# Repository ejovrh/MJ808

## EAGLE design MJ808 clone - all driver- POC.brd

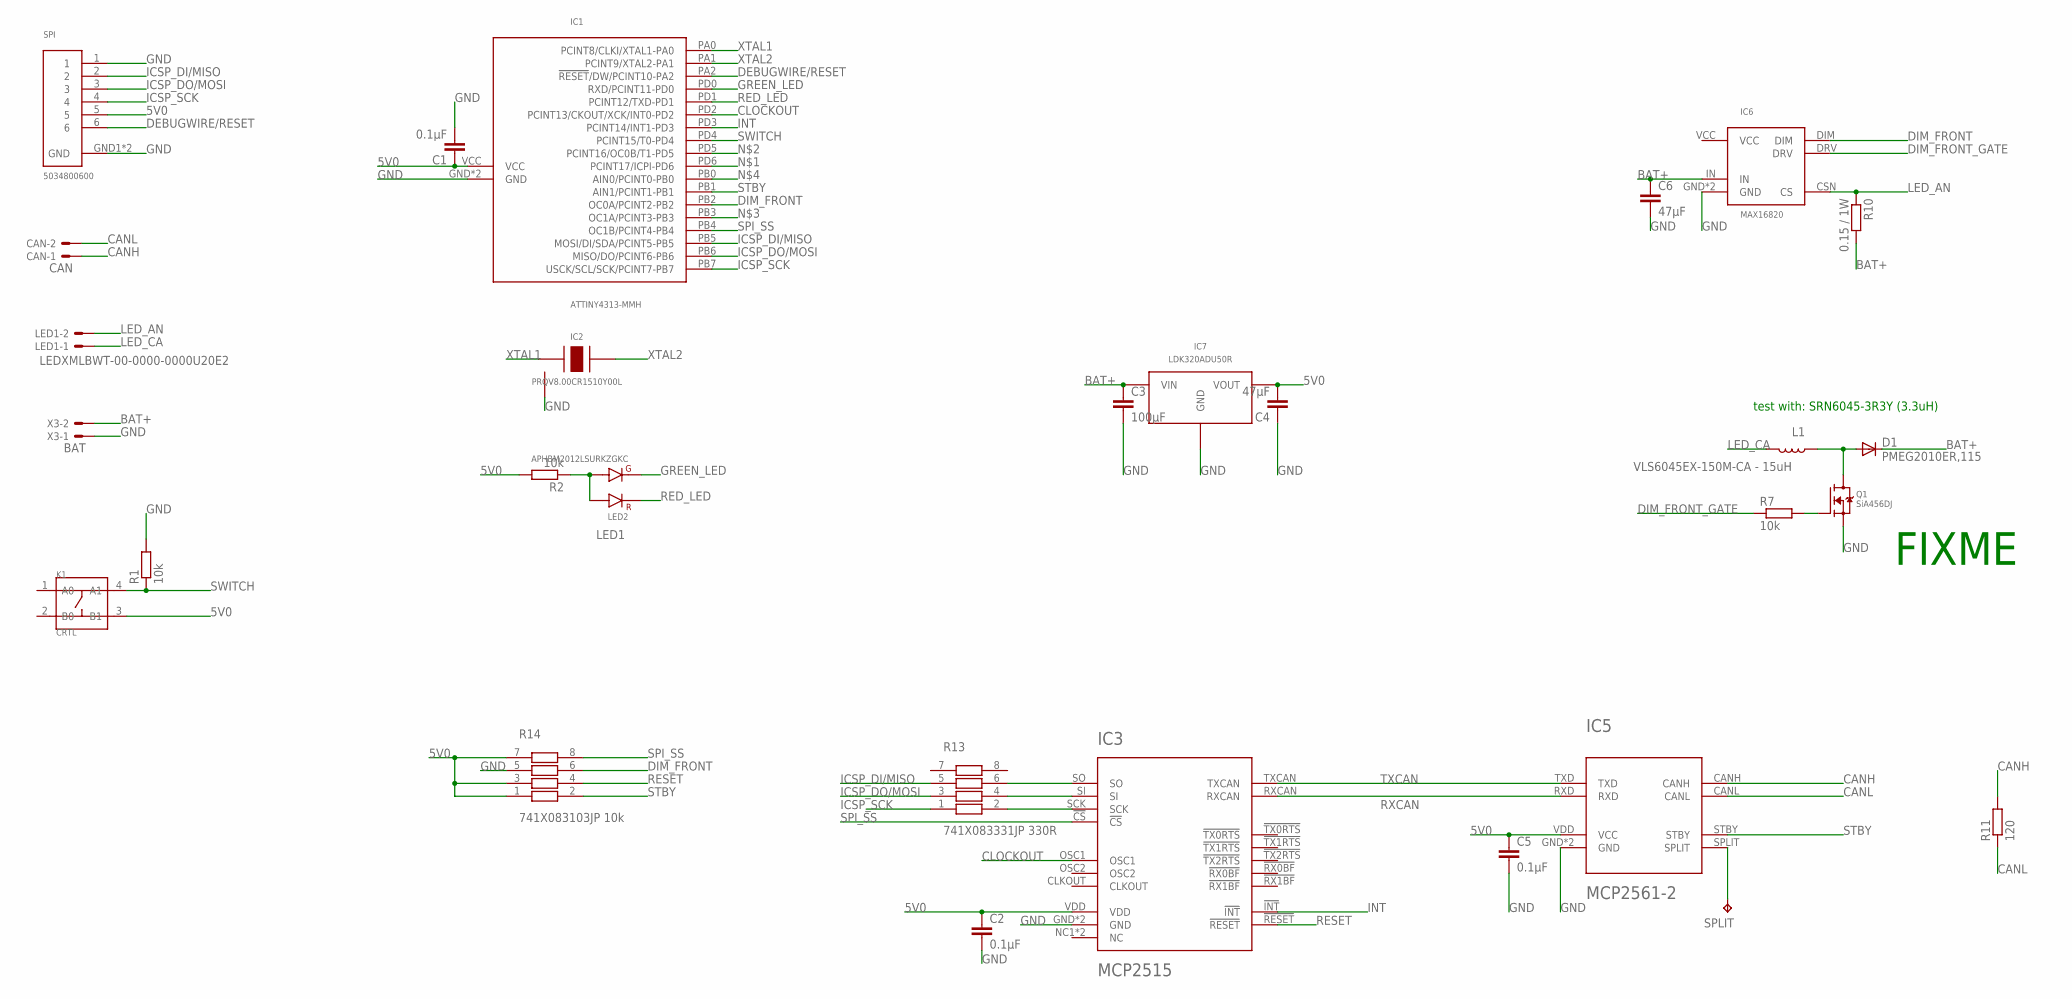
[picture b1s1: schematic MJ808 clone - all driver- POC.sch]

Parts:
C1, C2, C5: 0.1μF; C0402
C3: 100μF; C1206
C4, C6: 47μF; C0805
CAN: CAN; 22-23-2021
D1: PMEG2010ER,115; SOD123
IC1: ATTINY4313-MMH; VQFN-20
IC2: PRQV8.00CR1510Y00L; SMT
IC3: MCP2515; QFN20
IC5: MCP2561-2; DFN10
IC6: MAX16820; TDFN-6-EP
IC7: LDK320ADU50R; SOT-89
K1: CRTL; SW4-SMD-6.0X6.0X5.0MM
L1: VLS6045EX-150M-CA - 15uH; SRN6045
LED1: LEDXMLBWT-00-0000-0000U20E2; 22-23-2021
LED2: APHBM2012LSURKZGKC; SMD
Q1: SiA456DJ; SC-70-6
R1, R2, R7: 10k; R0402
R10: 0.15 / 1W; R1210
R11: 120; R0805
R13: 741X083331JP 330R; 0402
R14: 741X083103JP 10k; 0402
SPI: 5034800600; SMT
SPLIT: TPB2,54; B2,54
X3: BAT; 22-23-2021

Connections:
5V0: C1.1, C2.1, C4.2, C5.1, IC1.VCC, IC3.VDD, IC5.VDD (VCC), IC7.VOUT, K1.3 (B1), R2.2, R14.1, R14.3, R14.7, SPI.5
BAT+: C3.1, C6.1, D1.C, IC6.IN, IC7.VIN, R10.2, X3.2
CANH: CAN.1, IC5.CANH, R11.2
CANL: CAN.2, IC5.CANL, R11.1
CLOCKOUT: IC1.PD2 (PCINT13/CKOUT/XCK/INT0-PD2), IC3.OSC1
DEBUGWIRE/RESET: IC1.PA2 (!RESET!/DW/PCINT10-PA2), SPI.6
DIM_BRAKE_DRAIN: D1.A, L1.1, Q1.D
DIM_FRONT: IC1.PB2 (OC0A/PCINT2-PB2), IC6.DIM, R14.6
DIM_FRONT_GATE: IC6.DRV, R7.1
GATE: Q1.G, R7.2
GND: C1.2, C2.2, C3.2, C4.1, C5.2, C6.2, IC1.GND, IC1.GND1 (GND), IC2.GND, IC3.GND, IC3.GND6 (GND), IC5.GND, IC5.VSS (GND), IC6.GND, IC6.GND1 (GND), IC7.GND, Q1.S, R1.2, R14.5, SPI.1, SPI.GND1 (GND), SPI.GND2 (GND), X3.1
GREEN_LED: IC1.PD0 (RXD/PCINT11-PD0), LED2.3
ICSP_DI/MISO: IC1.PB5 (MOSI/DI/SDA/PCINT5-PB5), R13.5, SPI.2
ICSP_DO/MOSI: IC1.PB6 (MISO/DO/PCINT6-PB6), R13.3, SPI.3
ICSP_SCK: IC1.PB7 (USCK/SCL/SCK/PCINT7-PB7), R13.1, SPI.4
INT: IC1.PD3 (PCINT14/INT1-PD3), IC3.!INT!
LED1: LED2.1, LED2.4, R2.1
LED_AN: IC6.CSN (CS), LED1.2, R10.1
LED_CA: L1.2, LED1.1
RED_LED: IC1.PD1 (PCINT12/TXD-PD1), LED2.2
RESET: IC3.!RESET!, R14.4
RXCAN: IC3.RXCAN, IC5.RXD
SPI_MISO: IC3.SO, R13.6
SPI_MOSI: IC3.SI, R13.4
SPI_SCK: IC3.SCK, R13.2
SPI_SS: IC1.PB4 (OC1B/PCINT4-PB4), IC3.!CS!, R14.8
SPLIT: IC5.SPLIT, SPLIT.TP
STBY: IC1.PB1 (AIN1/PCINT1-PB1), IC5.STBY, R14.2
SWITCH: IC1.PD4 (PCINT15/T0-PD4), K1.4 (A1), R1.1
TXCAN: IC3.TXCAN, IC5.TXD
VCC: IC6.VCC
XTAL1: IC1.PA0 (PCINT8/CLKI/XTAL1-PA0), IC2.XTAL1
XTAL2: IC1.PA1 (PCINT9/XTAL2-PA1), IC2.XTAL2

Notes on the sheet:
FIXME
test with: SRN6045-3R3Y (3.3uH)

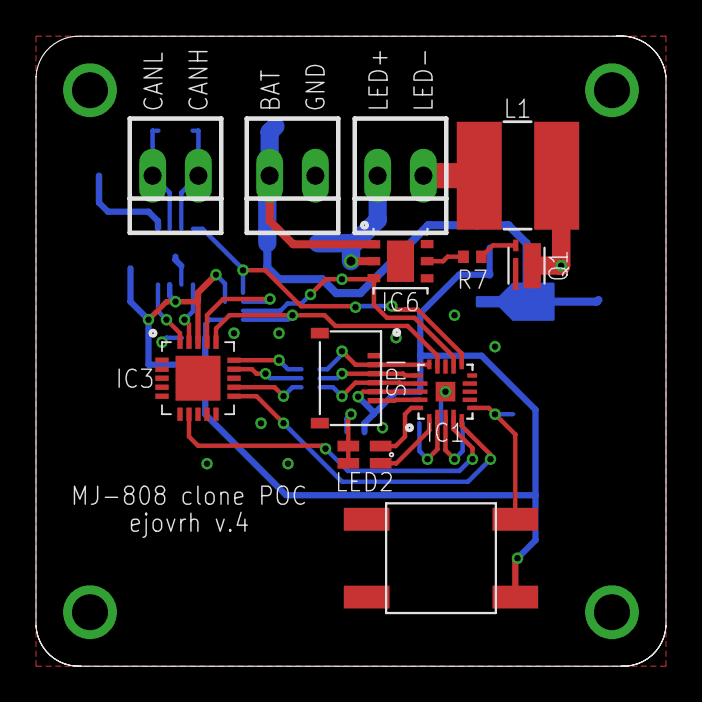
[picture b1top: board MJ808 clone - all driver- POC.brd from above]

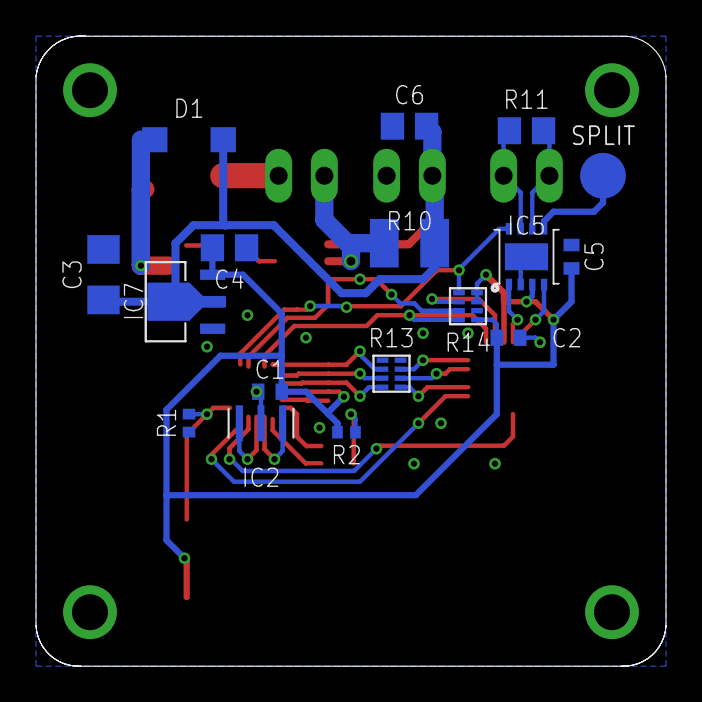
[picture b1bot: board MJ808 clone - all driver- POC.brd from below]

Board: 2 copper layers, 35.0 x 35.0 mm, 29 parts (17 on the bottom side), 32 nets.

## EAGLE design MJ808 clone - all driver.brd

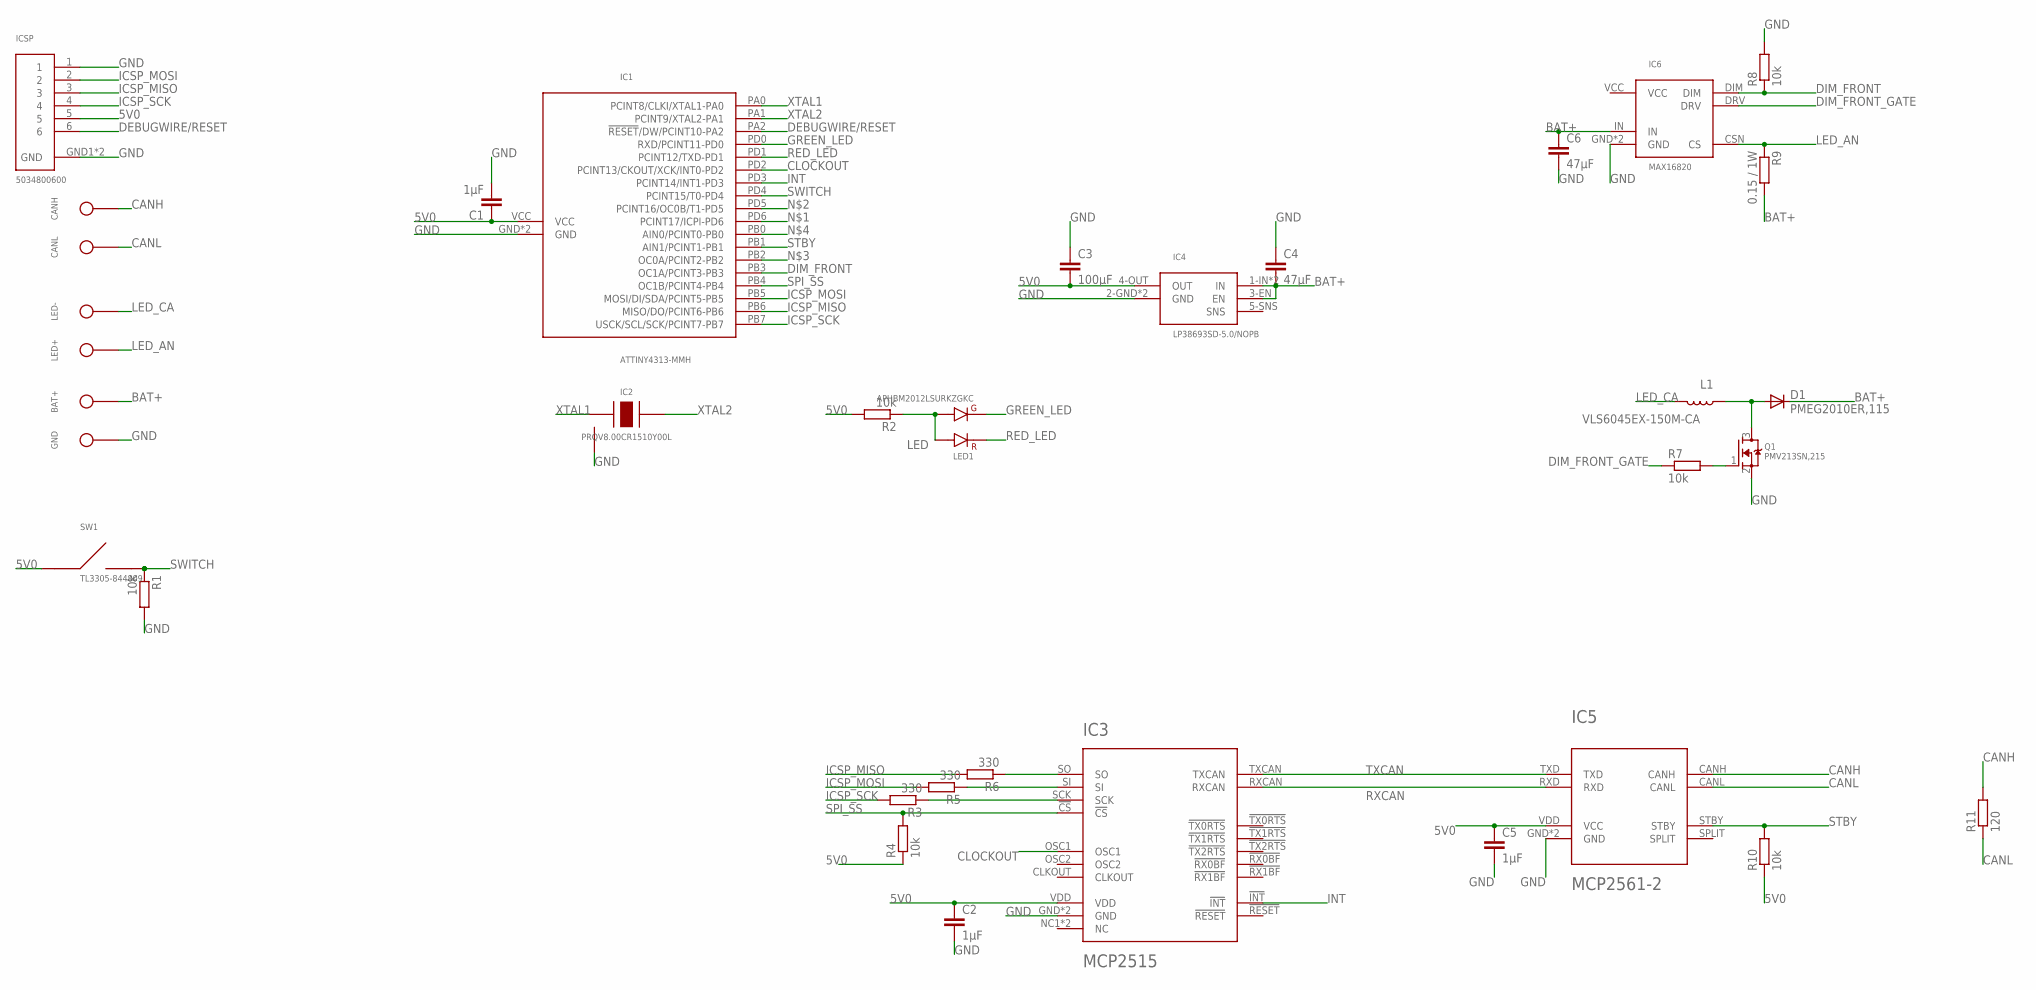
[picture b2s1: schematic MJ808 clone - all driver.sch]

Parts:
BAT+: LiIon + Terminal; TH
C1, C2, C5: 1μF; C0402
C3: 100μF; C1206
C4, C6: 47μF; C0805
CANH: CAN high; TH
CANL: CAN low; TH
D1: PMEG2010ER,115; SOD123
GND: LiIon - Terminal; TH
IC1: ATTINY4313-MMH; VQFN-20
IC2: PRQV8.00CR1510Y00L; SMT
IC3: MCP2515; QFN20
IC4: LP38693SD-5.0/NOPB; WSON6
IC5: MCP2561-2; DFN10
IC6: MAX16820; TDFN-6-EP
ICSP: 5034800600; SMT
L1: VLS6045EX-150M-CA; SRN6045
LED1: APHBM2012LSURKZGKC; SMD
LED+: LED anode; TH
LED-: LED cathode; TH
Q1: PMV213SN,215; SOT23
R1, R2, R4, R7, R8, R10: 10k; R0402
R3, R5, R6: 330; R0402
R9: 0.15 / 1W; R1210
R11: 120; R0805
SW1: TL3305-844809; SMD

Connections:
5V0: C1.1, C2.1, C3.2, C5.1, IC1.VCC, IC3.VDD, IC4.4-OUT (OUT), IC5.VDD (VCC), ICSP.5, R2.2, R4.1, R10.1, SW1.1, SW1.2
BAT+: BAT+.TP$1, C4.2, C6.1, D1.C, IC4.1-IN (IN), IC4.3-EN (EN), IC4.6-IN (IN), IC6.IN, R9.2
CANH: CANH.TP$1, IC5.CANH, R11.2
CANL: CANL.TP$1, IC5.CANL, R11.1
CLOCKOUT: IC1.PD2 (PCINT13/CKOUT/XCK/INT0-PD2), IC3.OSC1
DEBUGWIRE/RESET: IC1.PA2 (!RESET!/DW/PCINT10-PA2), ICSP.6
DIM_BRAKE_DRAIN: D1.A, L1.1, Q1.3 (D)
DIM_FRONT: IC1.PB3 (OC1A/PCINT3-PB3), IC6.DIM, R8.1
DIM_FRONT_GATE: IC6.DRV, R7.1
GATE: Q1.1 (G), R7.2
GND: C1.2, C2.2, C3.1, C4.1, C5.2, C6.2, GND.TP$1, IC1.GND, IC1.GND1 (GND), IC2.GND, IC3.GND, IC3.GND6 (GND), IC4.2-GND (GND), IC4.GND1 (GND), IC5.GND, IC5.VSS (GND), IC6.GND, IC6.GND1 (GND), ICSP.1, ICSP.GND1 (GND), ICSP.GND2 (GND), Q1.2 (S), R1.2, R8.2
GREEN_LED: IC1.PD0 (RXD/PCINT11-PD0), LED1.3
ICSP_MISO: IC1.PB6 (MISO/DO/PCINT6-PB6), ICSP.3, R6.2
ICSP_MOSI: IC1.PB5 (MOSI/DI/SDA/PCINT5-PB5), ICSP.2, R5.2
ICSP_SCK: IC1.PB7 (USCK/SCL/SCK/PCINT7-PB7), ICSP.4, R3.2
INT: IC1.PD3 (PCINT14/INT1-PD3), IC3.!INT!
LED: LED1.1, LED1.4, R2.1
LED_AN: IC6.CSN (CS), LED+.TP$1, R9.1
LED_CA: L1.2, LED-.TP$1
RED_LED: IC1.PD1 (PCINT12/TXD-PD1), LED1.2
RXCAN: IC3.RXCAN, IC5.RXD
SPI_MISO: IC3.SO, R6.1
SPI_MOSI: IC3.SI, R5.1
SPI_SCK: IC3.SCK, R3.1
SPI_SS: IC1.PB4 (OC1B/PCINT4-PB4), IC3.!CS!, R4.2
STBY: IC1.PB1 (AIN1/PCINT1-PB1), IC5.STBY, R10.2
SWITCH: IC1.PD4 (PCINT15/T0-PD4), R1.1, SW1.3, SW1.4
TXCAN: IC3.TXCAN, IC5.TXD
VCC: IC6.VCC
XTAL1: IC1.PA0 (PCINT8/CLKI/XTAL1-PA0), IC2.XTAL1
XTAL2: IC1.PA1 (PCINT9/XTAL2-PA1), IC2.XTAL2

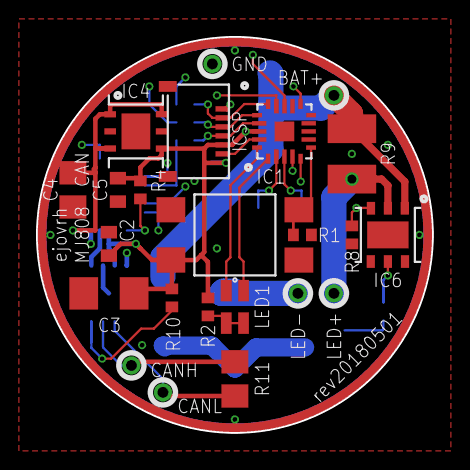
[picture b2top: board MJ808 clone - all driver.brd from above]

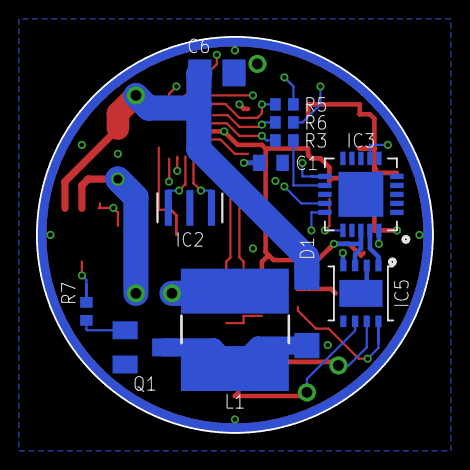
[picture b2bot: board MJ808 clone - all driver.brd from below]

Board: 4 copper layers, 22.0 x 22.0 mm, 35 parts (12 on the bottom side), 30 nets.

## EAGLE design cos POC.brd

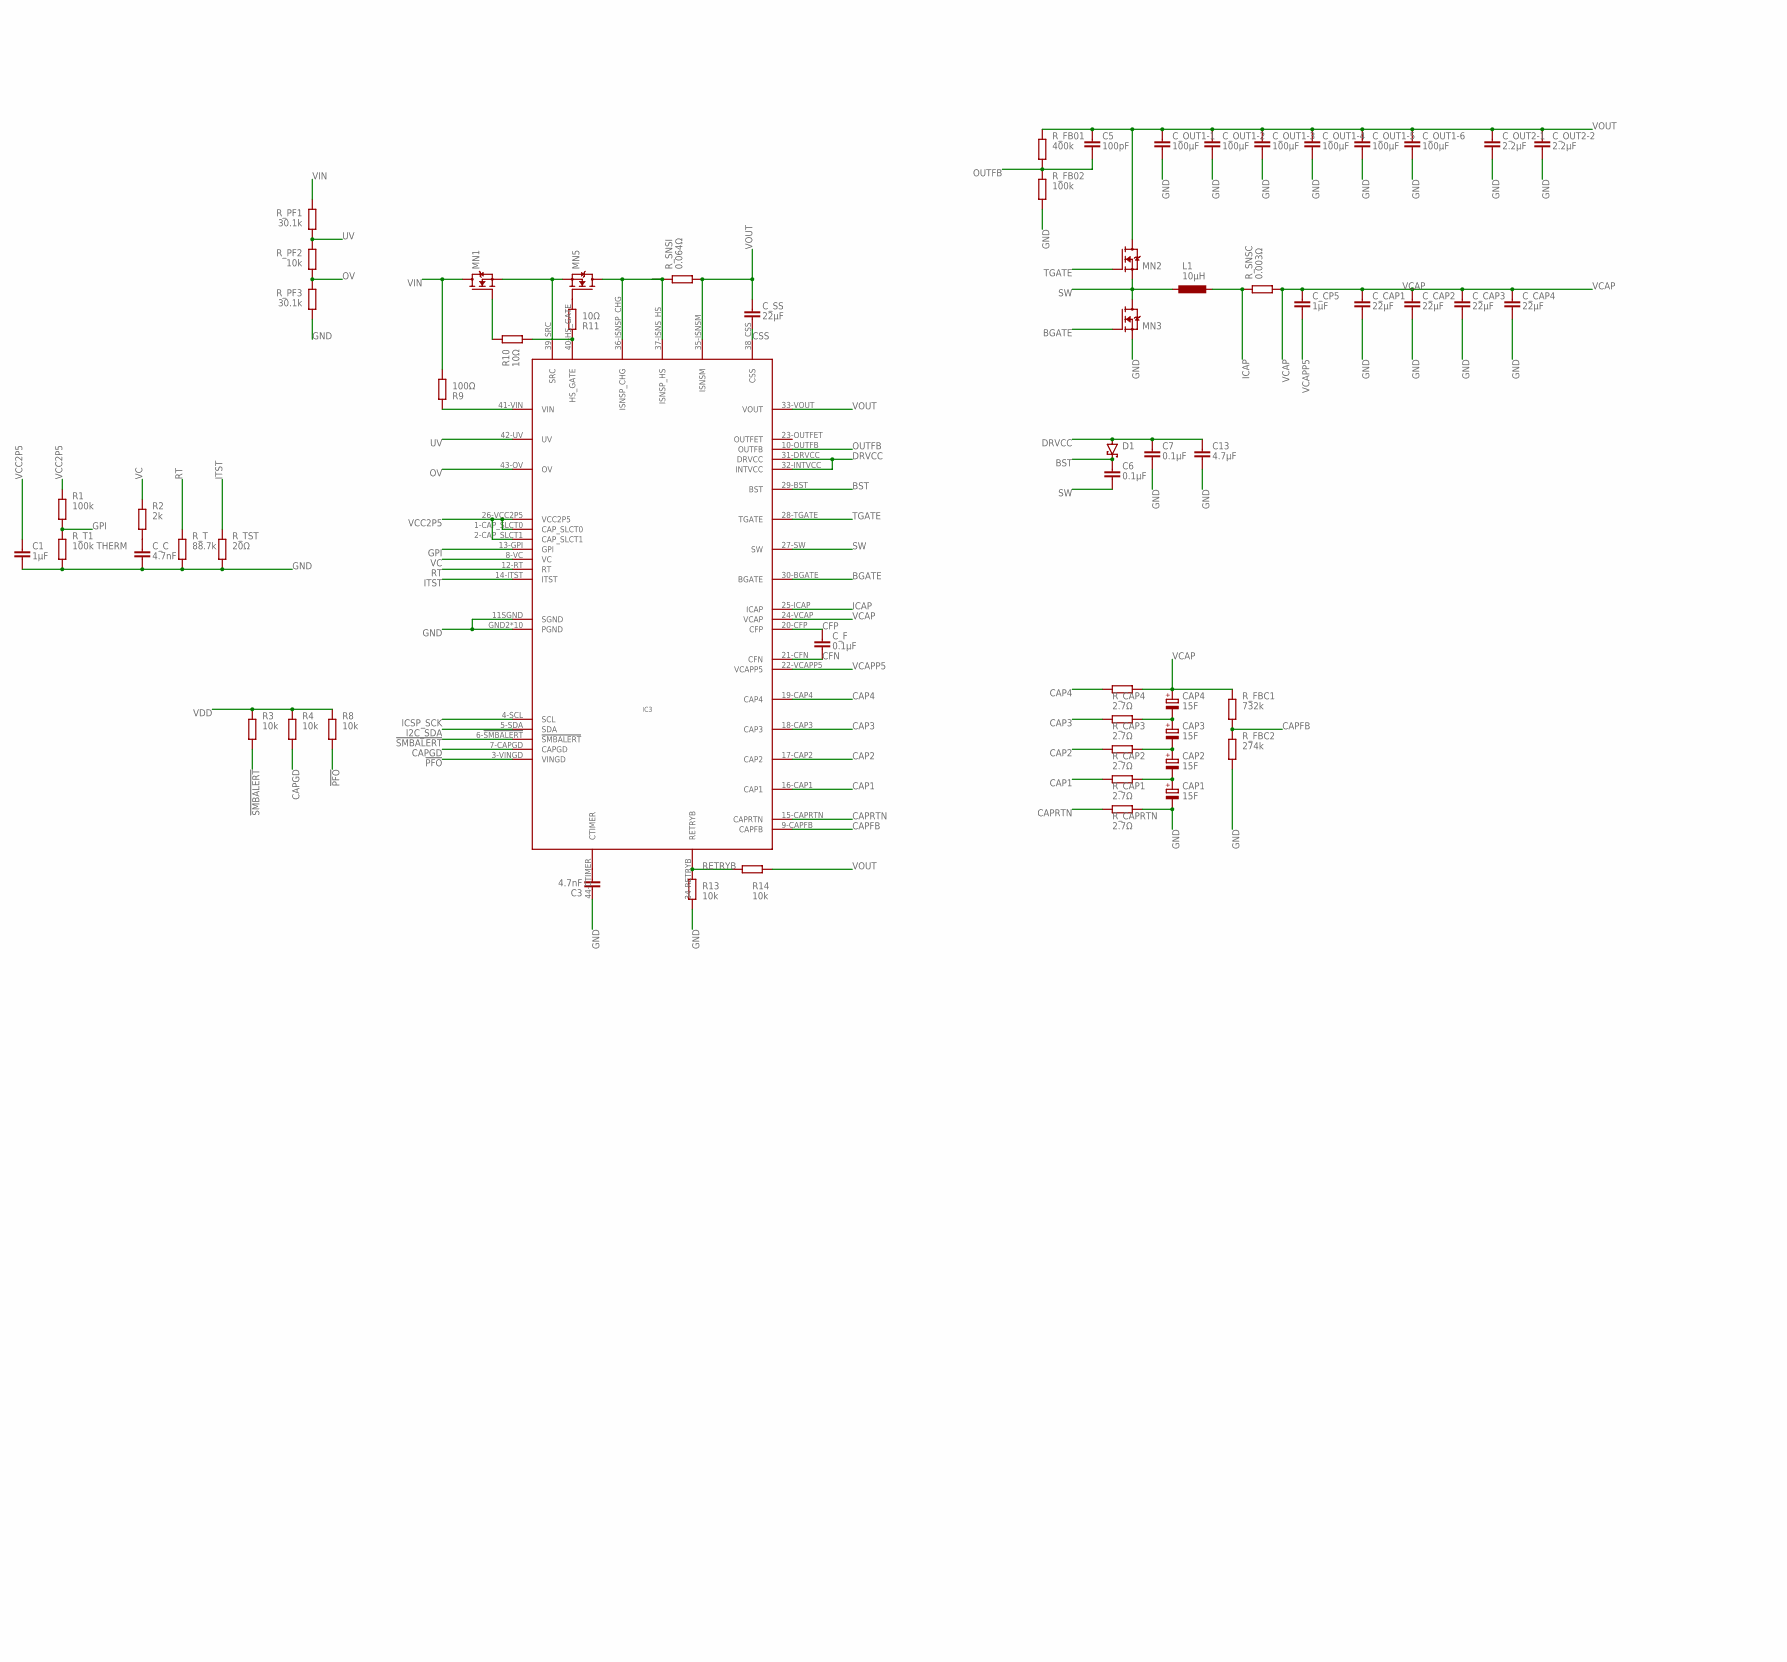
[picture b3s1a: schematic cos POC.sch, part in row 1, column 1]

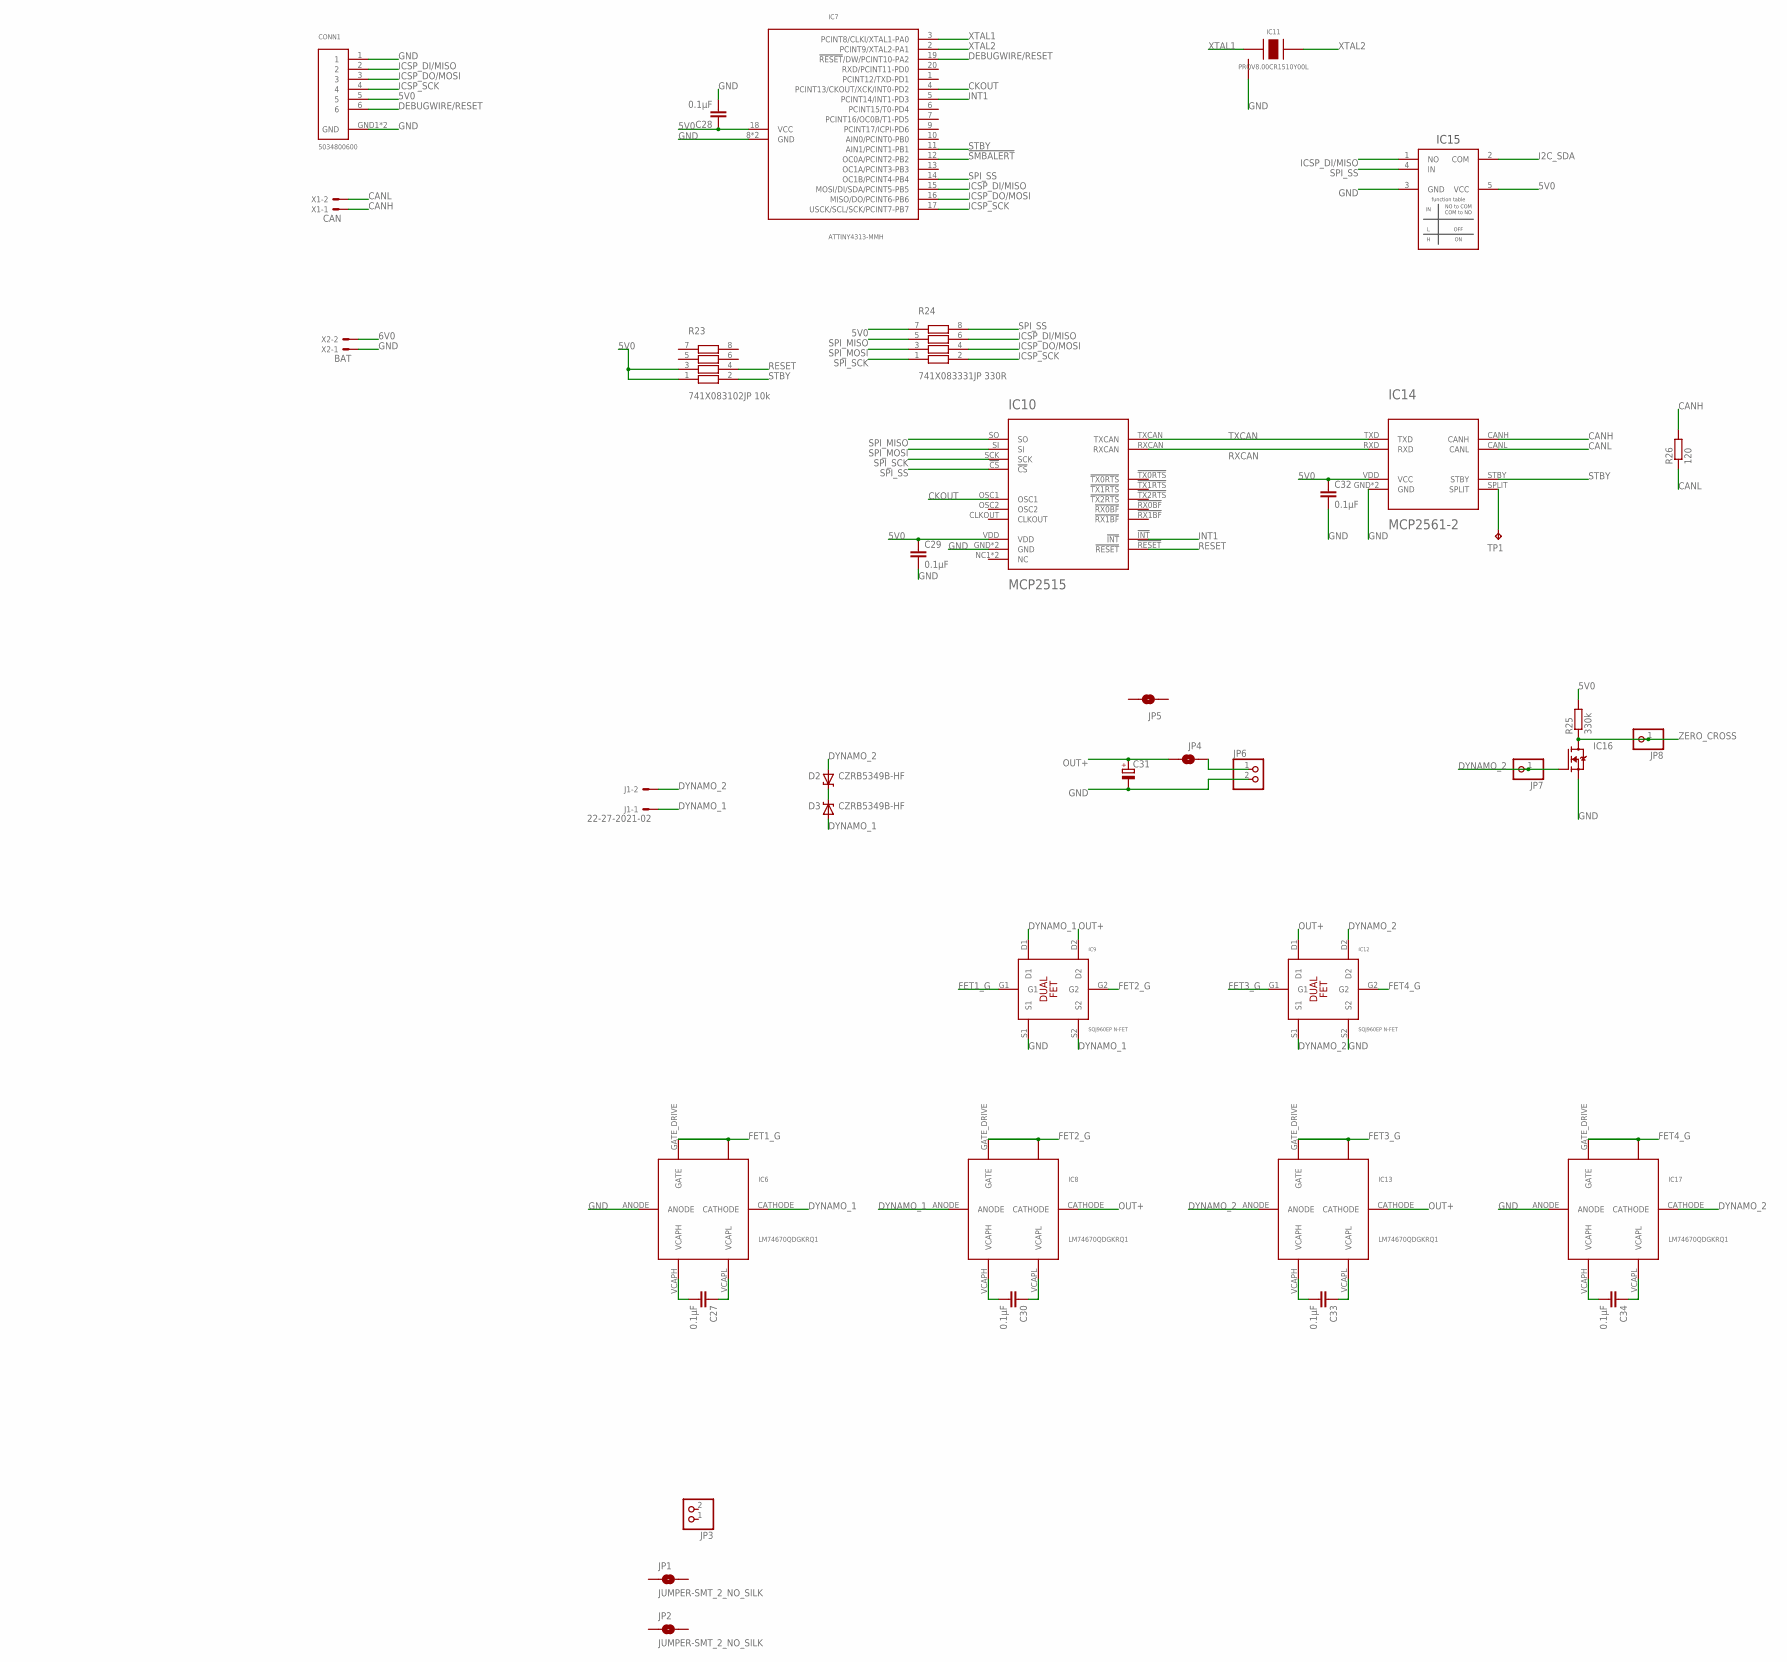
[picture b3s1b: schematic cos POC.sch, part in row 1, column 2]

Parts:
C1: 1μF; C0402
C3: 4.7nF; C0402
C5: 100pF; C0402
C6, C7, C28, C29, C32: 0.1μF; C0402
C13: 4.7μF; C0402
C27, C30, C33, C34: 0.1μF; C0805
C31: CPOL-EUB45181A; B45181A
CAP1, CAP2, CAP3, CAP4: 15F; E5-8,5
CONN1: 5034800600; SMT
C_C: 4.7nF; C0402
C_CAP1, C_CAP2, C_CAP3, C_CAP4: 22μF; C0402
C_CP5: 1μF; C0402
C_F: 0.1μF; C0402
C_OUT1-1, C_OUT1-2, C_OUT1-3, C_OUT1-4, C_OUT1-5, C_OUT1-6: 100μF; C0402
C_OUT2-1, C_OUT2-2: 2.2μF; C0402
C_SS: 22μF; C0402
D1: SCHOTTKY-DIODESMC; SMC
D2, D3: CZRB5349B-HF; DO-214
IC3: LTC3351; QFN44
IC6, IC8, IC13, IC17: LM74670QDGKRQ1; VSSOP-8
IC7: ATTINY4313-MMH; VQFN-20
IC9, IC12: SQJ960EP N-FET; SO-8L
IC10: MCP2515; QFN20
IC11: PRQV8.00CR1510Y00L; SMT
IC14: MCP2561-2; DFN10
IC15: TS5A1066SOT-23; SOT-23
IC16: SIA456DJ; SC-70-6
J1: 22-27-2021-02; 6410-02
JP1, JP2, JP4, JP5: JUMPER-SMT_2_NO_SILK; SMT-JUMPER_2_NO_SILK
JP3, JP6: PINHD-1X2; 1X02
JP7, JP8: PINHD-1X1; 1X01
L1: 10μH; L1812
MN1, MN2, MN3, MN5: SIA456DJ; SC-70-6
R1: 100k; R0402
R2: 2k; R0402
R3, R4, R8, R13, R14: 10k; R0402
R9: 100Ω; R0402
R10, R11: 10Ω; R0402
R23: 741X083102JP 10k; 0402-4R
R24: 741X083331JP 330R; 0402-4R
R25: 330k; R0805
R26: 120; R0805
R_CAP1, R_CAP2, R_CAP3, R_CAP4: 2.7Ω; R0402
R_CAPRTN: 2.7Ω; R0402
R_FB01: 400k; R0402
R_FB02: 100k; R0402
R_FBC1: 732k; R0402
R_FBC2: 274k; R0402
R_PF1, R_PF3: 30.1k; R0402
R_PF2: 10k; R0402
R_SNSC: 0.003Ω; R0402
R_SNSI: 0.064Ω; R0402
R_T: 88.7k; R0402
R_T1: 100k THERM; R0402
R_TST: 20Ω; R0402
TP1: TPB2,54; B2,54
X1: CAN; 22-23-2021
X2: BAT; 22-23-2021

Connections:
5V0: C28.1, C29.1, C32.1, CONN1.5, IC7.18 (VCC), IC10.VDD, IC14.VDD (VCC), IC15.5 (VCC), R23.1, R23.3, R24.7, R25.2
!PFO!: IC3.3-VINGD (VINGD), R8.2
!SMBALERT!: IC3.6-!SMBALERT! (!SMBALERT!), IC7.12 (OC0A/PCINT2-PB2), R3.2
BGATE: IC3.30-BGATE (BGATE), MN3.3G (G)
BST: C6.1, D1.C, IC3.29-BST (BST)
CANH: IC14.CANH, R26.2, X1.1
CANL: IC14.CANL, R26.1, X1.2
CAP1: IC3.16-CAP1 (CAP1), R_CAP1.1
CAP2: IC3.17-CAP2 (CAP2), R_CAP2.1
CAP3: IC3.18-CAP3 (CAP3), R_CAP3.1
CAP4: IC3.19-CAP4 (CAP4), R_CAP4.1
CAPFB: IC3.9-CAPFB (CAPFB), R_FBC1.1, R_FBC2.2
CAPGD: IC3.7-CAPGD (CAPGD), R4.2
CAPRTN: IC3.15-CAPRTN (CAPRTN), R_CAPRTN.1
CFN: C_F.2, IC3.21-CFN (CFN)
CFP: C_F.1, IC3.20-CFP (CFP)
CKOUT: IC7.4 (PCINT13/CKOUT/XCK/INT0-PD2), IC10.OSC1
CSS: C_SS.2, IC3.38_CSS (CSS)
CTIMER: C3.2, IC3.44-CTIMER (CTIMER)
DEBUGWIRE/RESET: CONN1.6, IC7.19 (!RESET!/DW/PCINT10-PA2)
DRVCC: C7.1, C13.1, D1.A, IC3.31-DRVCC (DRVCC), IC3.32-INTVCC (INTVCC)
DYNAMO_1: D3.AN, IC6.CATHODE, IC8.ANODE, IC9.D1, IC9.S2, J1.1
DYNAMO_2: D2.AN, IC12.D2, IC12.S1, IC13.ANODE, IC16.3G (G), IC17.CATHODE, J1.2, JP7.1
FET1_G: IC6.GATE_DRIVE (GATE), IC6.GATE_PULLD, IC9.G1
FET2_G: IC8.GATE_DRIVE (GATE), IC8.GATE_PULLD, IC9.G2
FET3_G: IC12.G1, IC13.GATE_DRIVE (GATE), IC13.GATE_PULLD
FET4_G: IC12.G2, IC17.GATE_DRIVE (GATE), IC17.GATE_PULLD
GND: C1.2, C3.1, C7.2, C13.2, C28.2, C29.2, C31.-, C32.2, CAP1.-, CONN1.1, CONN1.GND1 (GND), CONN1.GND2 (GND), C_C.2, C_CAP1.2, C_CAP2.2, C_CAP3.2, C_CAP4.2, C_OUT1-1.2, C_OUT1-2.2, C_OUT1-3.2, C_OUT1-4.2, C_OUT1-5.2, C_OUT1-6.2, C_OUT2-1.2, C_OUT2-2.2, IC3.11SGND (SGND), IC3.GND2 (PGND), IC3.GND3 (PGND), IC3.GND4 (PGND), IC3.GND5 (PGND), IC3.GND6 (PGND), IC3.GND7 (PGND), IC3.GND8 (PGND), IC3.GND9 (PGND), IC3.GND10 (PGND), IC3.PGND, IC6.ANODE, IC7.8 (GND), IC7.GND, IC9.S1, IC10.GND, IC10.GND6 (GND), IC11.GND, IC12.S2, IC14.GND, IC14.VSS (GND), IC15.3 (GND), IC16.4S (S), IC16.S, IC17.ANODE, JP6.2, MN3.4S (S), MN3.S, R13.2, R_CAPRTN.2, R_FB02.2, R_FBC2.1, R_PF3.2, R_T.2, R_T1.2, R_TST.2, X2.1
GPI: IC3.13-GPI (GPI), R1.2, R_T1.1
I2C_SDA: IC3.5-SDA (SDA), IC15.2 (COM)
ICAP: IC3.25-ICAP (ICAP), L1.2, R_SNSC.1
ICSP_DI/MISO: CONN1.2, IC7.15 (MOSI/DI/SDA/PCINT5-PB5), IC15.1 (NO), R24.6
ICSP_DO/MOSI: CONN1.3, IC7.16 (MISO/DO/PCINT6-PB6), R24.4
ICSP_SCK: CONN1.4, IC3.4-SCL (SCL), IC7.17 (USCK/SCL/SCK/PCINT7-PB7), R24.2
INT1: IC7.5 (PCINT14/INT1-PD3), IC10.!INT!
ITST: IC3.14-ITST (ITST), R_TST.1
unnamed: IC3.39_SRC (SRC), MN1.4S (S), MN1.S, MN5.4S (S), MN5.S
unnamed: MN1.3G (G), R10.1
unnamed: C27.2, IC6.VCAPH
unnamed: JP1.1, JP4.2, JP6.1
unnamed: IC3.36-ISNSP_CHG (ISNSP_CHG), IC3.37-ISNS_HS (ISNSP_HS), MN5.1D (D), MN5.2D (D), MN5.5D (D), MN5.6D (D), MN5.D, R_SNSI.1
unnamed: CAP3.+, CAP4.-, R_CAP3.2
unnamed: CAP2.+, CAP3.-, R_CAP2.2
unnamed: C27.1, IC6.VCAPL
unnamed: C34.2, IC17.VCAPH
unnamed: C34.1, IC17.VCAPL
unnamed: C33.1, IC13.VCAPL
unnamed: C33.2, IC13.VCAPH
unnamed: C30.1, IC8.VCAPL
unnamed: C30.2, IC8.VCAPH
unnamed: CAP1.+, CAP2.-, R_CAP1.2
unnamed: MN5.3G (G), R11.2
unnamed: C_C.1, R2.2
unnamed: IC3.40-HS_GATE (HS_GATE), R10.2, R11.1
unnamed: IC3.41-VIN (VIN), R9.1
unnamed: IC14.SPLIT, TP1.TP
OUT+: C31.+, IC8.CATHODE, IC9.D2, IC12.D1, IC13.CATHODE, JP4.1
OUTFB: C5.2, IC3.10-OUTFB (OUTFB), R_FB01.2, R_FB02.1
OV: IC3.43-OV (OV), R_PF2.2, R_PF3.1
RESET: IC10.!RESET!, R23.4
RETRYB: IC3.34-RETRYB (RETRYB), R13.1, R14.1
RT: IC3.12-RT (RT), R_T.1
RXCAN: IC10.RXCAN, IC14.RXD
SPI_MISO: IC10.SO, R24.5
SPI_MOSI: IC10.SI, R24.3
SPI_SCK: IC10.SCK, R24.1
SPI_SS: IC7.14 (OC1B/PCINT4-PB4), IC10.!CS!, IC15.4 (IN), R24.8
STBY: IC7.11 (AIN1/PCINT1-PB1), IC14.STBY, R23.2
SW: C6.2, IC3.27-SW (SW), L1.1, MN2.4S (S), MN2.S, MN3.1D (D), MN3.2D (D), MN3.5D (D), MN3.6D (D), MN3.D
TGATE: IC3.28-TGATE (TGATE), MN2.3G (G)
TXCAN: IC10.TXCAN, IC14.TXD
UV: IC3.42-UV (UV), R_PF1.2, R_PF2.1
VC: IC3.8-VC (VC), R2.1
VCAP: CAP4.+, C_CAP1.1, C_CAP2.1, C_CAP3.1, C_CAP4.1, C_CP5.1, IC3.24-VCAP (VCAP), R_CAP4.2, R_FBC1.2, R_SNSC.2
VCAPP5: C_CP5.2, IC3.22-VCAPP5 (VCAPP5)
VCC2P5: C1.1, IC3.1-CAP_SLCT0 (CAP_SLCT0), IC3.2-CAP_SLCT1 (CAP_SLCT1), IC3.26-VCC2P5 (VCC2P5), R1.1
VDD: R3.1, R4.1, R8.1
VIN: JP1.2, MN1.1D (D), MN1.2D (D), MN1.5D (D), MN1.6D (D), MN1.D, R9.2, R_PF1.1
XTAL1: IC7.3 (PCINT8/CLKI/XTAL1-PA0), IC11.XTAL1
XTAL2: IC7.2 (PCINT9/XTAL2-PA1), IC11.XTAL2
ZENER_COMMON: D2.CAT, D3.CAT
ZERO_CROSS: IC16.1D (D), IC16.2D (D), IC16.5D (D), IC16.6D (D), IC16.D, JP8.1, R25.1

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
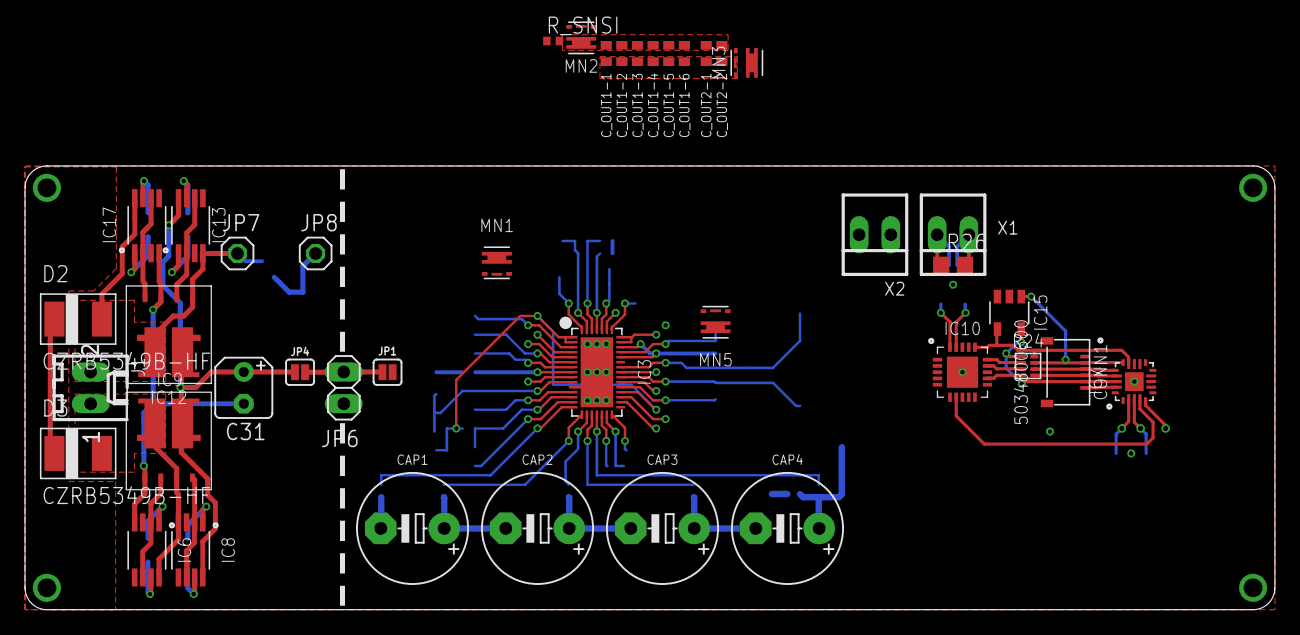
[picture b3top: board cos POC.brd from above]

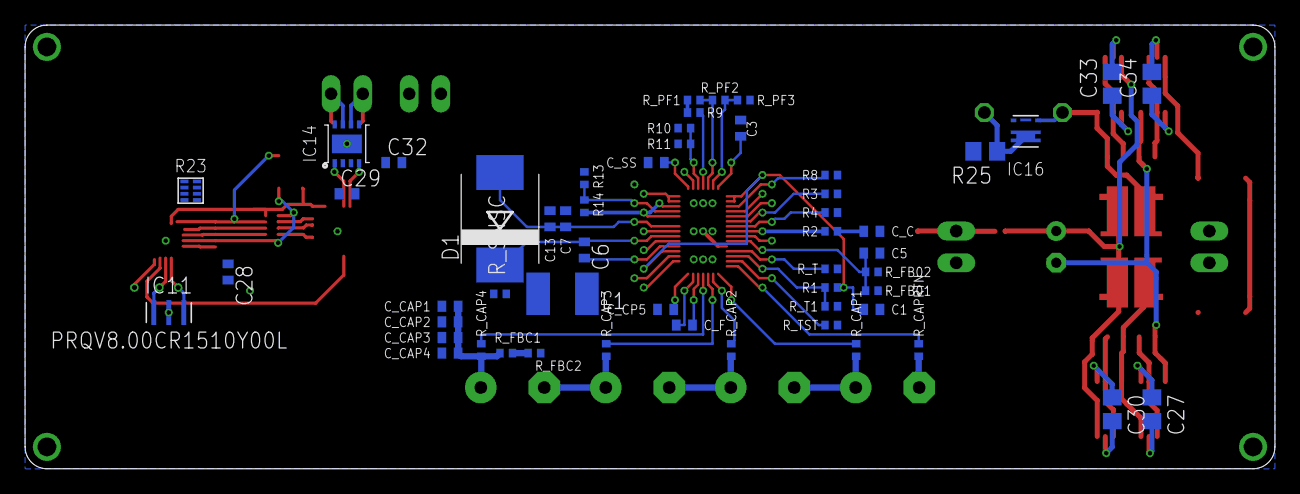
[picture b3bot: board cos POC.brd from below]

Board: 2 copper layers, 100.0 x 35.5 mm, 95 parts (54 on the bottom side), 82 nets.

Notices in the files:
parts and their libraries:
SparkFun-Coils: Licensing: Creative Commons ShareAlike 4.0 International - https://creativecommons.org/licenses/by-sa/4.0
